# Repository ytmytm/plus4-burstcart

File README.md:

# BurstCart - Fast serial cartridge for C16/116/Plus4

This Plus/4 cartridge implements both fast serial burst for 1570/1571/1581 drives and a parallel connection for the 1541 drive, enabling high-speed data transfers.

<a href="https://www.youtube.com/watch?v=kfF7x9RVxz8" target="_blank">
 
 <p><small>Click for video</small></p>
</a>

## About

The project started as a response to a question from **[Plus/4 World Forum](https://plus4world.powweb.com/forum.php?postid=52378)**.

In order to use the Burst (fast serial) protocol as implemented on the C128, we need a bidirectional hardware serial port.

The published version uses VIA 6522 chips, which are still relatively easy to obtain. The additional logic addresses a VIA hardware bug that can lead to framing errors and lost bits when the serial port is externally clocked, as is the case with the fast serial burst protocol.

The single IEC port should be connected to the pass-through serial port on the last disk drive in the chain, looping back to the computer.

VIA Port A and lines CA1/CA2 are also used as a parallel connection for 1541 parallel burst with hardware handshake. The order of signals on the J3 connector for a ribbon cable is compatible with parallel cables known from the C64, particularly DolphinDOS.

VIA Port B is not used, except for bit 0, which controls the direction of the serial port.

Other attempts included in the repository are:

### CPLD

This is an attempt to drop legacy chips altogether.

Due to the limited number of gates, it only implements small parts of the CIA, such as timer A with a fixed rate, the hardware serial port, and the status register. The implementation does only what it necessary to make burst protocol work: to be able to send a byte via burst to enable burst protocol and to receive bytes on serial port with external clock.

### CIA (6526) - abandoned

This seemed obvious as CBM themselves added CIA just for this purpose to 1571. However, the timing differences made it impossible to use the CIA reliably with the screen on.

These chips are also hard to obtain.

The PCB had enough space for two IEC ports as a passthrough.

## Hardware

### VIA

KiCad 6.0 project files are available in the [`burstcart-via/kicad/`](burstcart-via/kicad/) directory.

Schematic is available as [`burstcart-via.pdf`](burstcart-via/kicad/plots/burstcart-via.pdf) in the `burstcart-via/kicad/plots/` directory.

Gerber files for manufacturing are available from [`burstcart-via/kicad/plots/`](burstcart-via/kicad/plots/) directory.

### CPLD

KiCad 6.0 project files are available in the [`burstcart-cpld/kicad/`](burstcart-cpld/kicad/) directory.

Schematic is available as [`burstcart-cpld.pdf`](burstcart-cpld/kicad/plots/burstcart-cpld-44.pdf) in the `burstcart-cpld/kicad/plots/` directory.

Gerber files for manufacturing are available from [`burstcart-cpld/kicad/plots/`](burstcart-cpld/kicad/plots/) directory.

## Firmware 

### VIA

The firmware for the GAL22V10 programmable logic device is provided as a compiled JEDEC file [`BURSTCART-VIA.jed`](burstcart-via/gal/BURSTCART-VIA.jed).

The source code for the GAL logic is written in CUPL and available as [`burstcart-via.pld`](burstcart-via/gal/burstcart-via.pld). This file contains the logic equations that implement the address decoding and serial port direction control.

The GAL firmware fixes VIA's address at `$FDA0-$FDAF` range.

### CPLD

The CPLD firmware is also provided as a compiled JEDEC file [`CIA.jed`](burstcart-cpld/hdl/ciasdr-hdl/cia.jed).

The source code is written in Verilog for XILINX ISE. All the project files are provided in [`ciasdr-hdl`](burstcart-cpld/hdl/ciasdr-hdl).

The firmware fixes CPLD address at `$FD90-$FD9F` range.

## Software

### EPROM

The GAL chip on the VIA version does not have enough space to support 64K ROMs as C1/C2 cartridges, so only 32K is visible to the computer at any given time as C1.

You can use 32K chips; for the 64K version, the 32K banks can be selected using a switch connected to JP4.

The CPLD version can address both C1 and C2 cartridges, so all 64K is available.

The **[Parobek](https://github.com/ytmytm/plus4-parobek)** project provides a ROM that supports various fastloaders for BurstCart:

- autodetected fast serial burst for 1570/1571/1581
- parallel cable loader for 1541
- even faster parallel cable loader for 1541 with [1541-RAMBOard](https://github.com/ytmytm/1541-RAMBOardII) patched ROM
- [tcbm2sd fastloader](https://github.com/ytmytm/plus4-tcbm2sd) for both device numbers
- 1551 fastloader for both device numbers
- DOS wedge
- embedded Directory Browser

Be sure to choose correct ROM version - for VIA or CPLD.

## VIA PCB jumpers

There are three jumpers on the VIA PCB:

- JP1 determines how the `/IRQ` line is connected to the VIA. For W65C22S, it should go through a diode; for all other 6522 versions, it can be connected directly, and `D1` can be omitted.
- JP2 chooses the clock for VIA - `phi0` or `phi2` (default)
- JP3 chooses the clock for GAL - `phi0` (default) or `phi2`
- JP4 controls line A15 for the EPROM and chooses which 32K half of a 64K ROM will appear as cartridge C1

## Theory of operation

### Fast serial

The burst mode protocol were originally developed by Commodore for the C128 and 1571/1581 drives. It uses the hardware serial port available on VIA and CIA chips. The data is transmitted over the IEC data line, with the hardware clock controlled by the sender and routed through the (otherwise unused) SRQ line. Changes in the IEC clock line are used as a handshake signal.

This was not available on the 1541 due to a hardware bug in the 6522 chips.

This project fixes the bug with a 74LS74 latch. Another 74LS126 chip is needed to buffer the input/output and provide the necessary open collector outputs on the external side for both the clock and data lines. The direction of the bus is controlled by port B bit 0 (PB0) pulled high to make it input as a default after reset.

The single IEC port on the VIA cartridge has only the hardware data and clock lines connected, as well as a common GND.

The CPLD cartridge has dual daisy-chained IEC ports, so you can connect the computer's serial port to cartridge and continue from the second port to all other IEC devices.

### Parallel cable

The 1541 drive's VIA#1 port A is unused. On the C64, this is connected to the User Port, along with two hardware handshake lines, providing the fastest possible connection between the VIA and CIA.

Here we connect it to port A as well. Note that on the BurstCart side, the handshake lines are connected to CA1/CA2 corresponding to port A, but to CA2/CB1 on the 1541 side. This is not symmetrical because on the 1541, CA1 from VIA#1 was already used for another purpose.

## Additional Resources

All files necessary for manufacturing, including Gerbers, schematic, GAL firmware, and ROM, can be found in the [GitHub releases section](https://github.com/ytmytm/plus4-burstcart/releases).

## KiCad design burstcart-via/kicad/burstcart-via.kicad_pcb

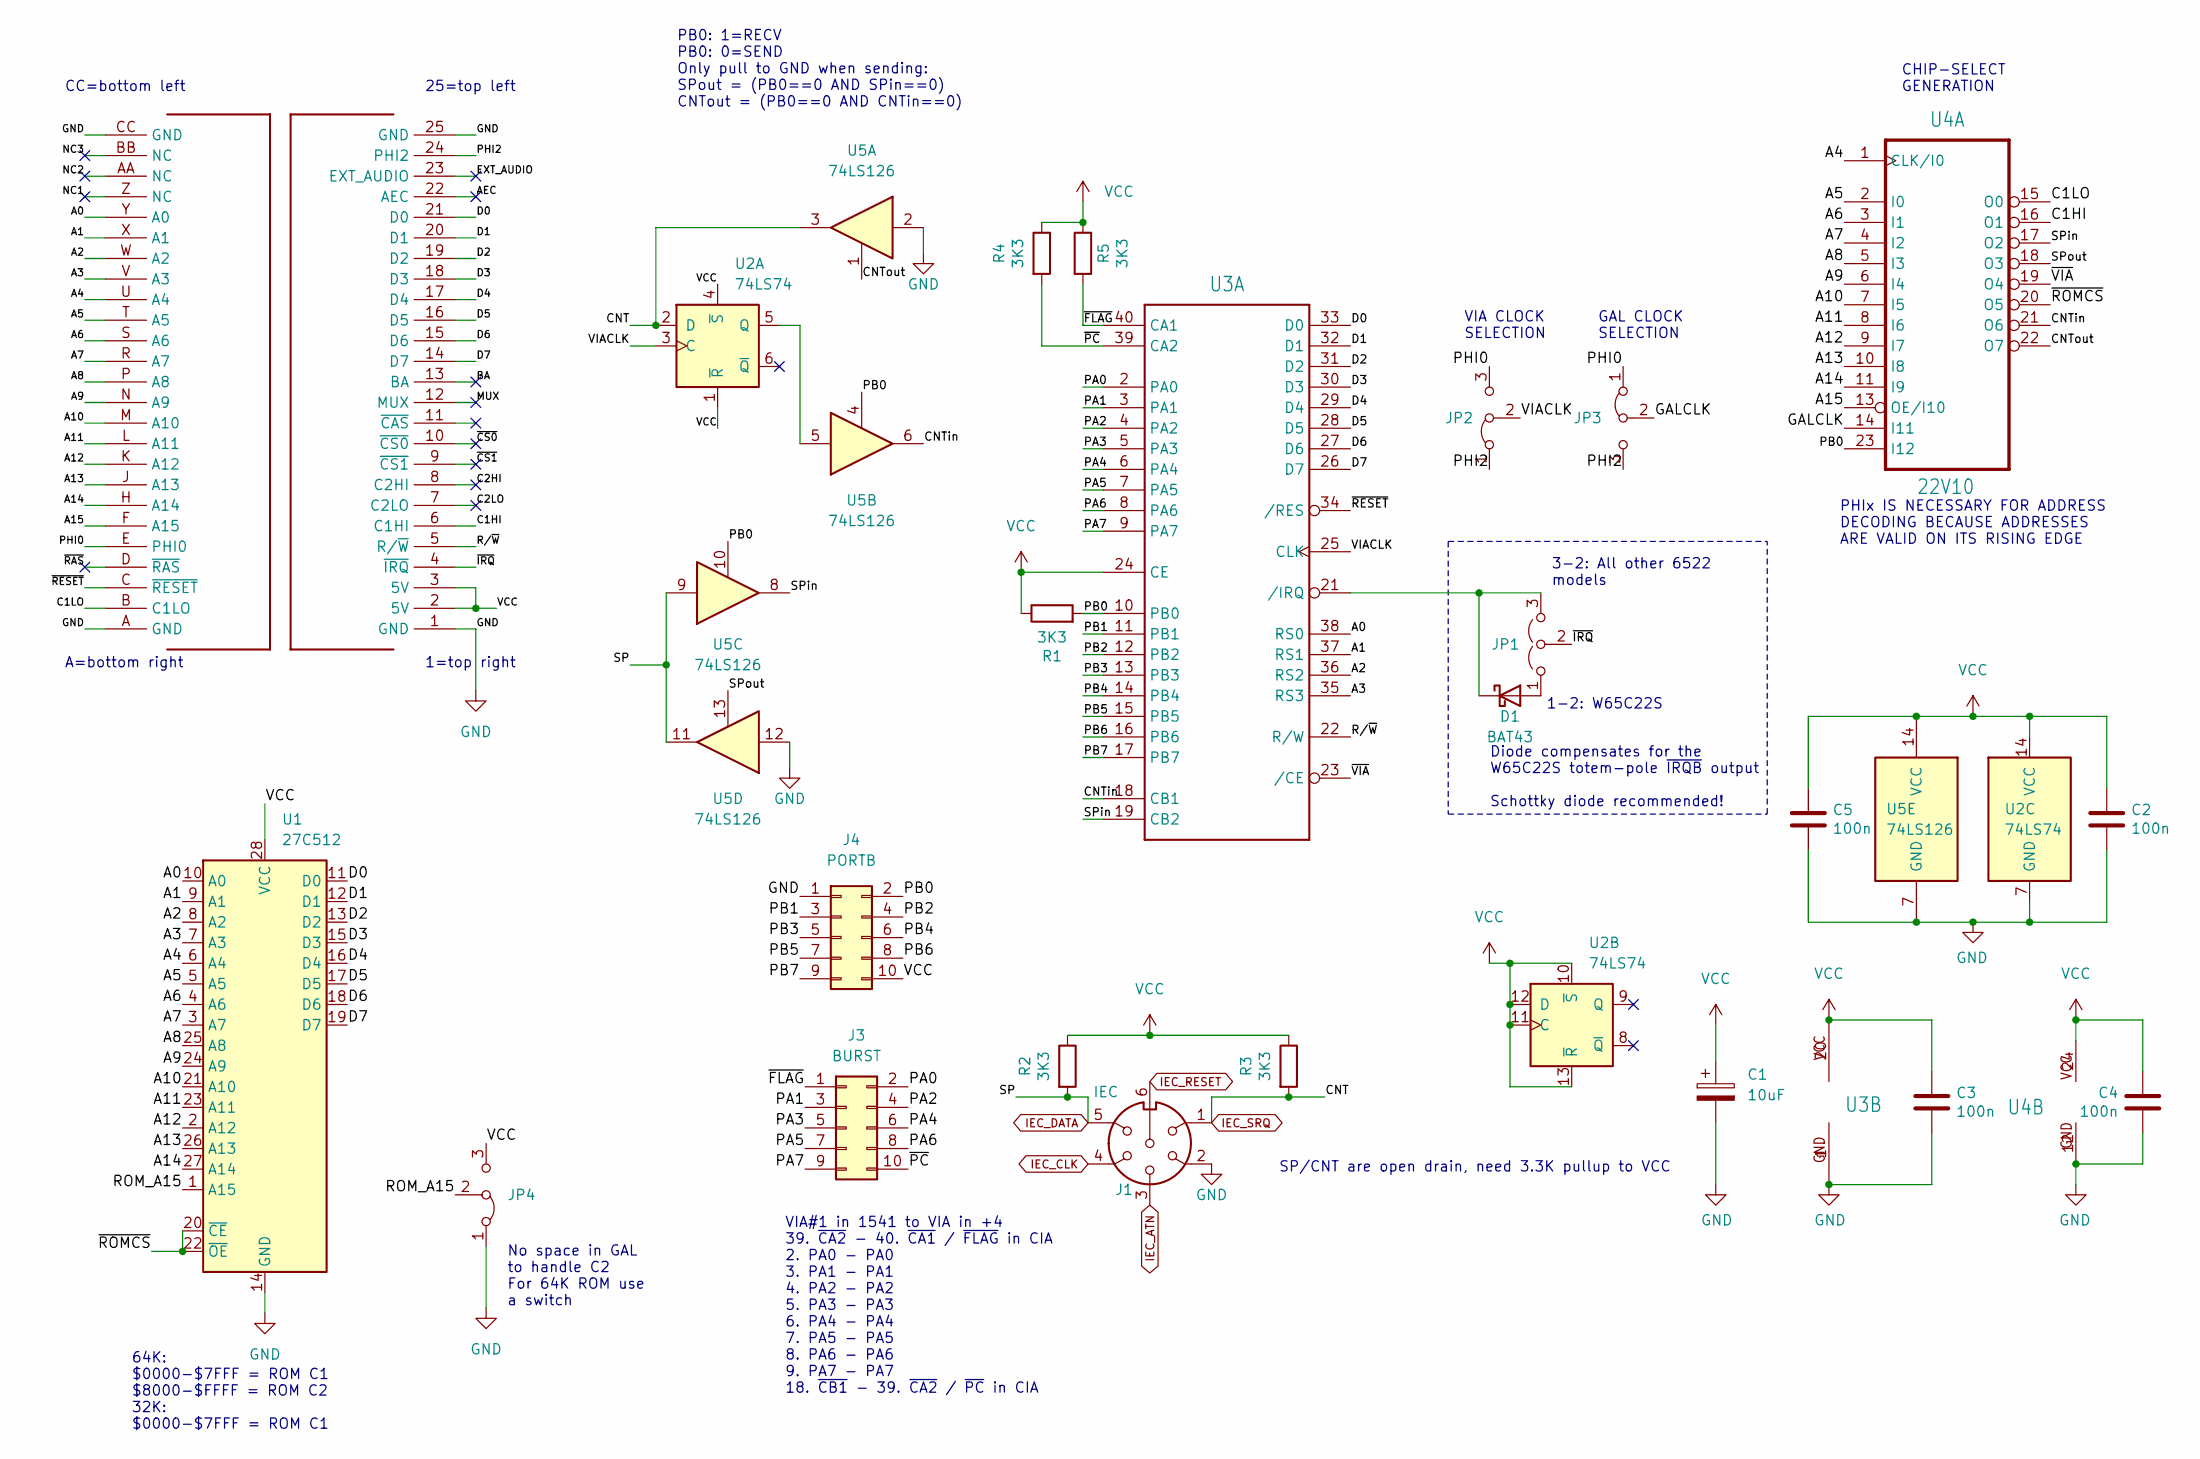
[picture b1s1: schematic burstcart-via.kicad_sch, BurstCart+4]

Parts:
C1: 10uF; CP_Radial_D5.0mm_P2.00mm
C2, C3, C4, C5: 470p; C_Disc_D7.0mm_W2.5mm_P5.00mm; MouserPN 810-FG28C0G1H471JNT6
D1: BAT43; D_DO-35_SOD27_P7.62mm_Horizontal
J1: IEC; DIN6
J3: BURST; PinHeader_2x05_P2.54mm_Vertical
J4: PORTB; PinHeader_2x05_P2.54mm_Vertical
JP1: Jumper_3_Open; SolderJumper-3_P1.3mm_Open_RoundedPad1.0x1.5mm_NumberLabels
JP2, JP3: Jumper_3_Bridged12; SolderJumper-3_P1.3mm_Bridged12_Pad1.0x1.5mm_NumberLabels
JP4: Jumper_3_Bridged12; PinHeader_1x03_P2.54mm_Vertical
R1, R2, R3, R4, R5: 3K3; R_Axial_DIN0207_L6.3mm_D2.5mm_P10.16mm_Horizontal
U1: 27C512; DIP-28_W15.24mm_Socket
U2: 74LS74; DIP-14_W7.62mm_Socket
U3: 6522; DIP-40_W15.24mm_Socket
U4: 22V10; DIP-24_W7.62mm_Socket
U5: 74LS126; DIP-14_W7.62mm_Socket
U$1: C16_CARTRIDGE; C16_CART

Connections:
/A0: U1.10 (A0), U3.38 (RS0), U$1.Y (A0)
/A1: U1.9 (A1), U3.37 (RS1), U$1.X (A1)
/A2: U1.8 (A2), U3.36 (RS2), U$1.W (A2)
/A3: U1.7 (A3), U3.35 (RS3), U$1.V (A3)
/A4: U1.6 (A4), U4.1 (CLK/I0), U$1.U (A4)
/A5: U1.5 (A5), U4.2 (I0), U$1.T (A5)
/A6: U1.4 (A6), U4.3 (I1), U$1.S (A6)
/A7: U1.3 (A7), U4.4 (I2), U$1.R (A7)
/A8: U1.25 (A8), U4.5 (I3), U$1.P (A8)
/A9: U1.24 (A9), U4.6 (I4), U$1.N (A9)
/A10: U1.21 (A10), U4.7 (I5), U$1.M (A10)
/A11: U1.23 (A11), U4.8 (I6), U$1.L (A11)
/A12: U1.2 (A12), U4.9 (I7), U$1.K (A12)
/A13: U1.26 (A13), U4.10 (I8), U$1.J (A13)
/A14: U1.27 (A14), U4.11 (I9), U$1.H (A14)
/A15: U4.13 (OE/I10), U$1.F (A15)
/AEC: U$1.22 (AEC)
/BA: U$1.13 (BA)
/C1HI: U4.16 (O1), U$1.6 (C1HI)
/C1LO: U4.15 (O0), U$1.B (C1LO)
/C2HI: U$1.8 (C2HI)
/C2LO: U$1.7 (C2LO)
/CNTin: U3.18 (CB1), U4.21 (O6), U5.6
/CNTout: U4.22 (O7), U5.1
/D0: U1.11 (D0), U3.33 (D0), U$1.21 (D0)
/D1: U1.12 (D1), U3.32 (D1), U$1.20 (D1)
/D2: U1.13 (D2), U3.31 (D2), U$1.19 (D2)
/D3: U1.15 (D3), U3.30 (D3), U$1.18 (D3)
/D4: U1.16 (D4), U3.29 (D4), U$1.17 (D4)
/D5: U1.17 (D5), U3.28 (D5), U$1.16 (D5)
/D6: U1.18 (D6), U3.27 (D6), U$1.15 (D6)
/D7: U1.19 (D7), U3.26 (D7), U$1.14 (D7)
/EXT_AUDIO: U$1.23 (EXT_AUDIO)
/GALCLK: JP3.2 (C), U4.14 (I11)
/MUX: U$1.12 (MUX)
/NC1: U$1.Z (NC)
/NC2: U$1.AA (NC)
/NC3: U$1.BB (NC)
/PA0: J3.2, U3.2 (PA0)
/PA1: J3.3, U3.3 (PA1)
/PA2: J3.4, U3.4 (PA2)
/PA3: J3.5, U3.5 (PA3)
/PA4: J3.6, U3.6 (PA4)
/PA5: J3.7, U3.7 (PA5)
/PA6: J3.8, U3.8 (PA6)
/PA7: J3.9, U3.9 (PA7)
/PB0: J4.2, R1.2, U3.10 (PB0), U4.23 (I12), U5.4, U5.10
/PB1: J4.3, U3.11 (PB1)
/PB2: J4.4, U3.12 (PB2)
/PB3: J4.5, U3.13 (PB3)
/PB4: J4.6, U3.14 (PB4)
/PB5: J4.7, U3.15 (PB5)
/PB6: J4.8, U3.16 (PB6)
/PB7: J4.9, U3.17 (PB7)
/PHI0: JP2.3 (B), JP3.1 (A), U$1.E (PHI0)
/PHI2: JP2.1 (A), JP3.3 (B), U$1.24 (PHI2)
/ROM_A15: JP4.2 (C), U1.1 (A15)
/R/~W: U3.22 (R/W), U$1.5 (R/~W)
/SPin: U3.19 (CB2), U4.17 (O2), U5.8
/SPout: U4.18 (O3), U5.13
/VIACLK: JP2.2 (C), U2.3 (C), U3.25 (CLK)
/~CS0: U$1.10 (~CS0)
/~CS1: U$1.9 (~CS1)
/~FLAG: J3.1, R5.2, U3.40 (CA1)
/~IRQ: JP1.2 (C), U$1.4 (~IRQ)
/~PC: J3.10, R4.2, U3.39 (CA2)
/~RAS: U$1.D (~RAS)
/~RESET: U3.34 (/RES), U$1.C (~RESET)
/~ROMCS: U1.20 (~CE), U1.22 (~OE), U4.20 (O5)
/~VIA: U3.23 (/CE), U4.19 (O4)
GND: C1.2, C2.2, C3.2, C4.2, C5.2, J1.2, J4.1, JP4.1 (A), U1.14 (GND), U2.7 (GND), U3.1 (GND), U4.12 (GND), U5.2, U5.7 (GND), U5.12, U$1.1 (GND), U$1.25 (GND), U$1.A (GND), U$1.CC (GND)
IEC_ATN: J1.3
IEC_CLK: J1.4
IEC_DATA: J1.5, R2.2, U5.9, U5.11
IEC_RESET: J1.6
IEC_SRQ: J1.1, R3.2, U2.2 (D), U5.3
unnamed: D1.2 (A), JP1.1 (A)
unnamed: D1.1 (K), JP1.3 (B), U3.21 (/IRQ)
unnamed: U2.5 (Q), U5.5
VCC: C1.1, C2.1, C3.1, C4.1, C5.1, J4.10, JP4.3 (B), R1.1, R2.1, R3.1, R4.1, R5.1, U1.28 (VCC), U2.1 (~R), U2.4 (~S), U2.10 (~S), U2.11 (C), U2.12 (D), U2.13 (~R), U2.14 (VCC), U3.20 (VCC), U3.24 (CE), U4.24 (VCC), U5.14 (VCC), U$1.2 (5V), U$1.3 (5V)

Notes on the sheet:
25=top left
Diode compensates for the W65C22S totem-pole ~{IRQB} output Schottky diode recommended!
VIA CLOCK SELECTION
1-2: W65C22S
A=bottom right
SP/CNT are open drain, need 3.3K pullup to VCC
VIA#1 in 1541 to VIA in +4 39. ~{CA2} - 40. ~{CA1} / ~{FLAG} in CIA 2. PA0 - PA0 3. PA1 - PA1 4. PA2 - PA2 5. PA3 - PA3 6. PA4 - PA4 7. PA5 - PA5 8. PA6 - PA6 9. PA7 - PA7 18. ~{CB1} - 39. ~{CA2} / ~{PC} in CIA
PB0: 1=RECV PB0: 0=SEND Only pull to GND when sending: SPout = (PB0==0 AND SPin==0) CNTout = (PB0==0 AND CNTin==0)
GAL CLOCK SELECTION
CHIP-SELECT GENERATION
CC=bottom left
No space in GAL to handle C2 For 64K ROM use a switch
3-2: All other 6522 models
1=top right
PHIx IS NECESSARY FOR ADDRESS DECODING BECAUSE ADDRESSES ARE VALID ON ITS RISING EDGE
64K: $0000-$7FFF = ROM C1 $8000-$FFFF = ROM C2 32K: $0000-$7FFF = ROM C1

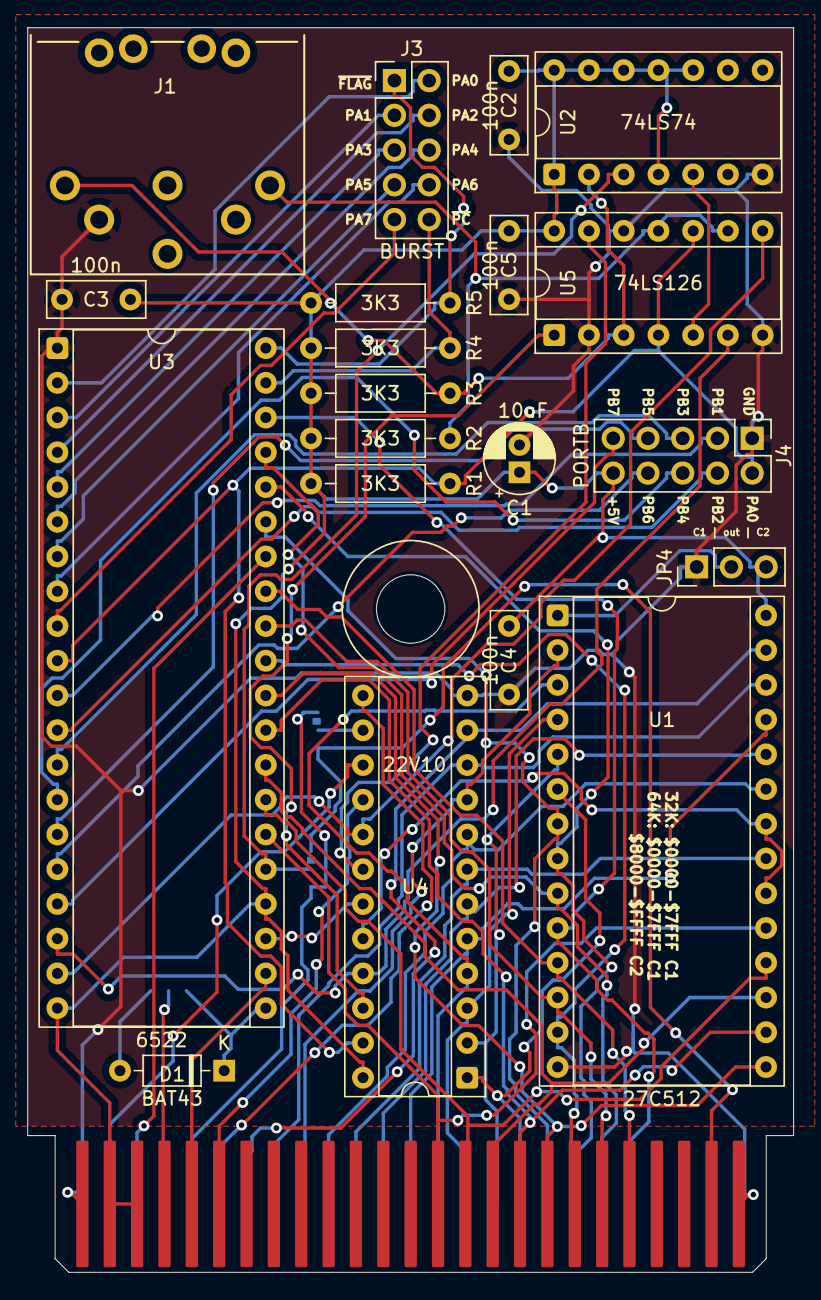
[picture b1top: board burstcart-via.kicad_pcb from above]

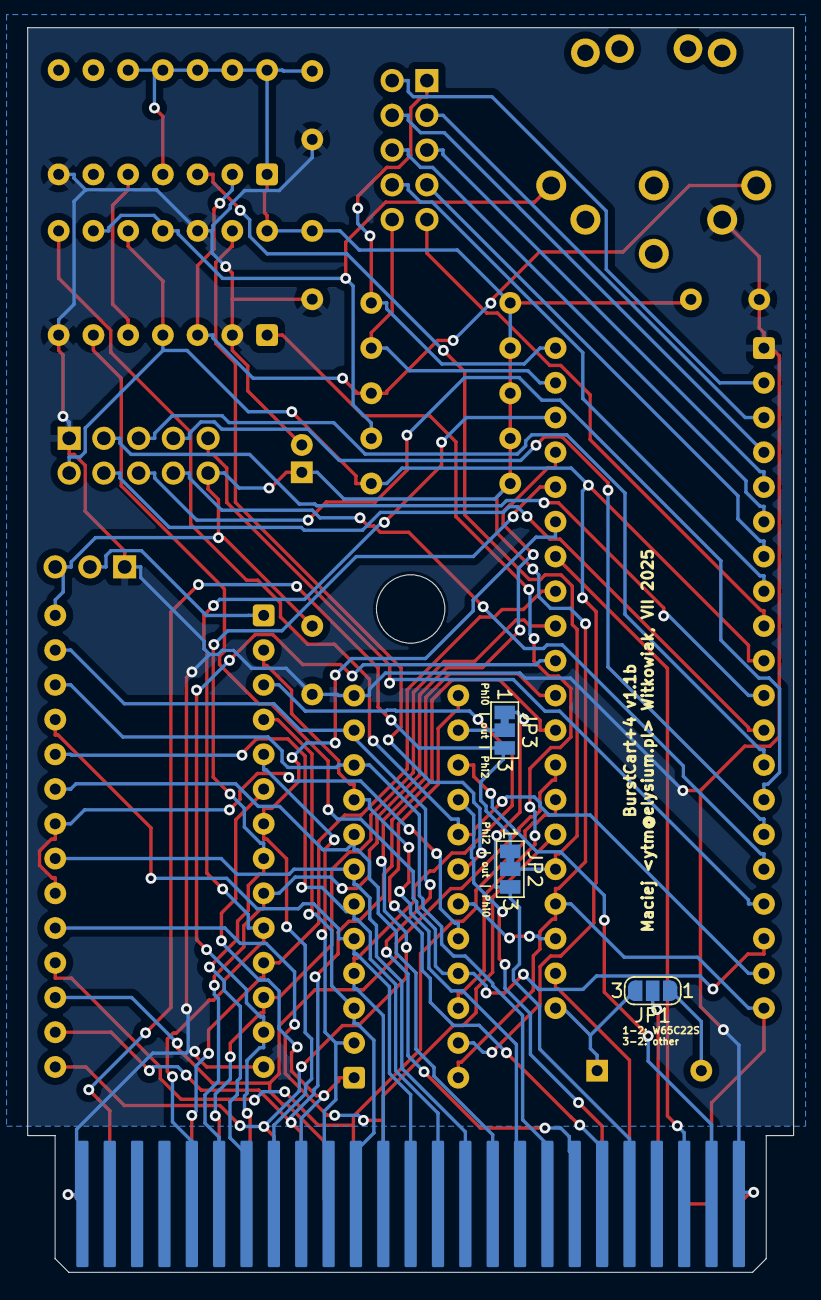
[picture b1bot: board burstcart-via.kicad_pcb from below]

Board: 2 copper layers, 56.0 x 91.0 mm, 24 parts (3 on the bottom side), 65 nets.

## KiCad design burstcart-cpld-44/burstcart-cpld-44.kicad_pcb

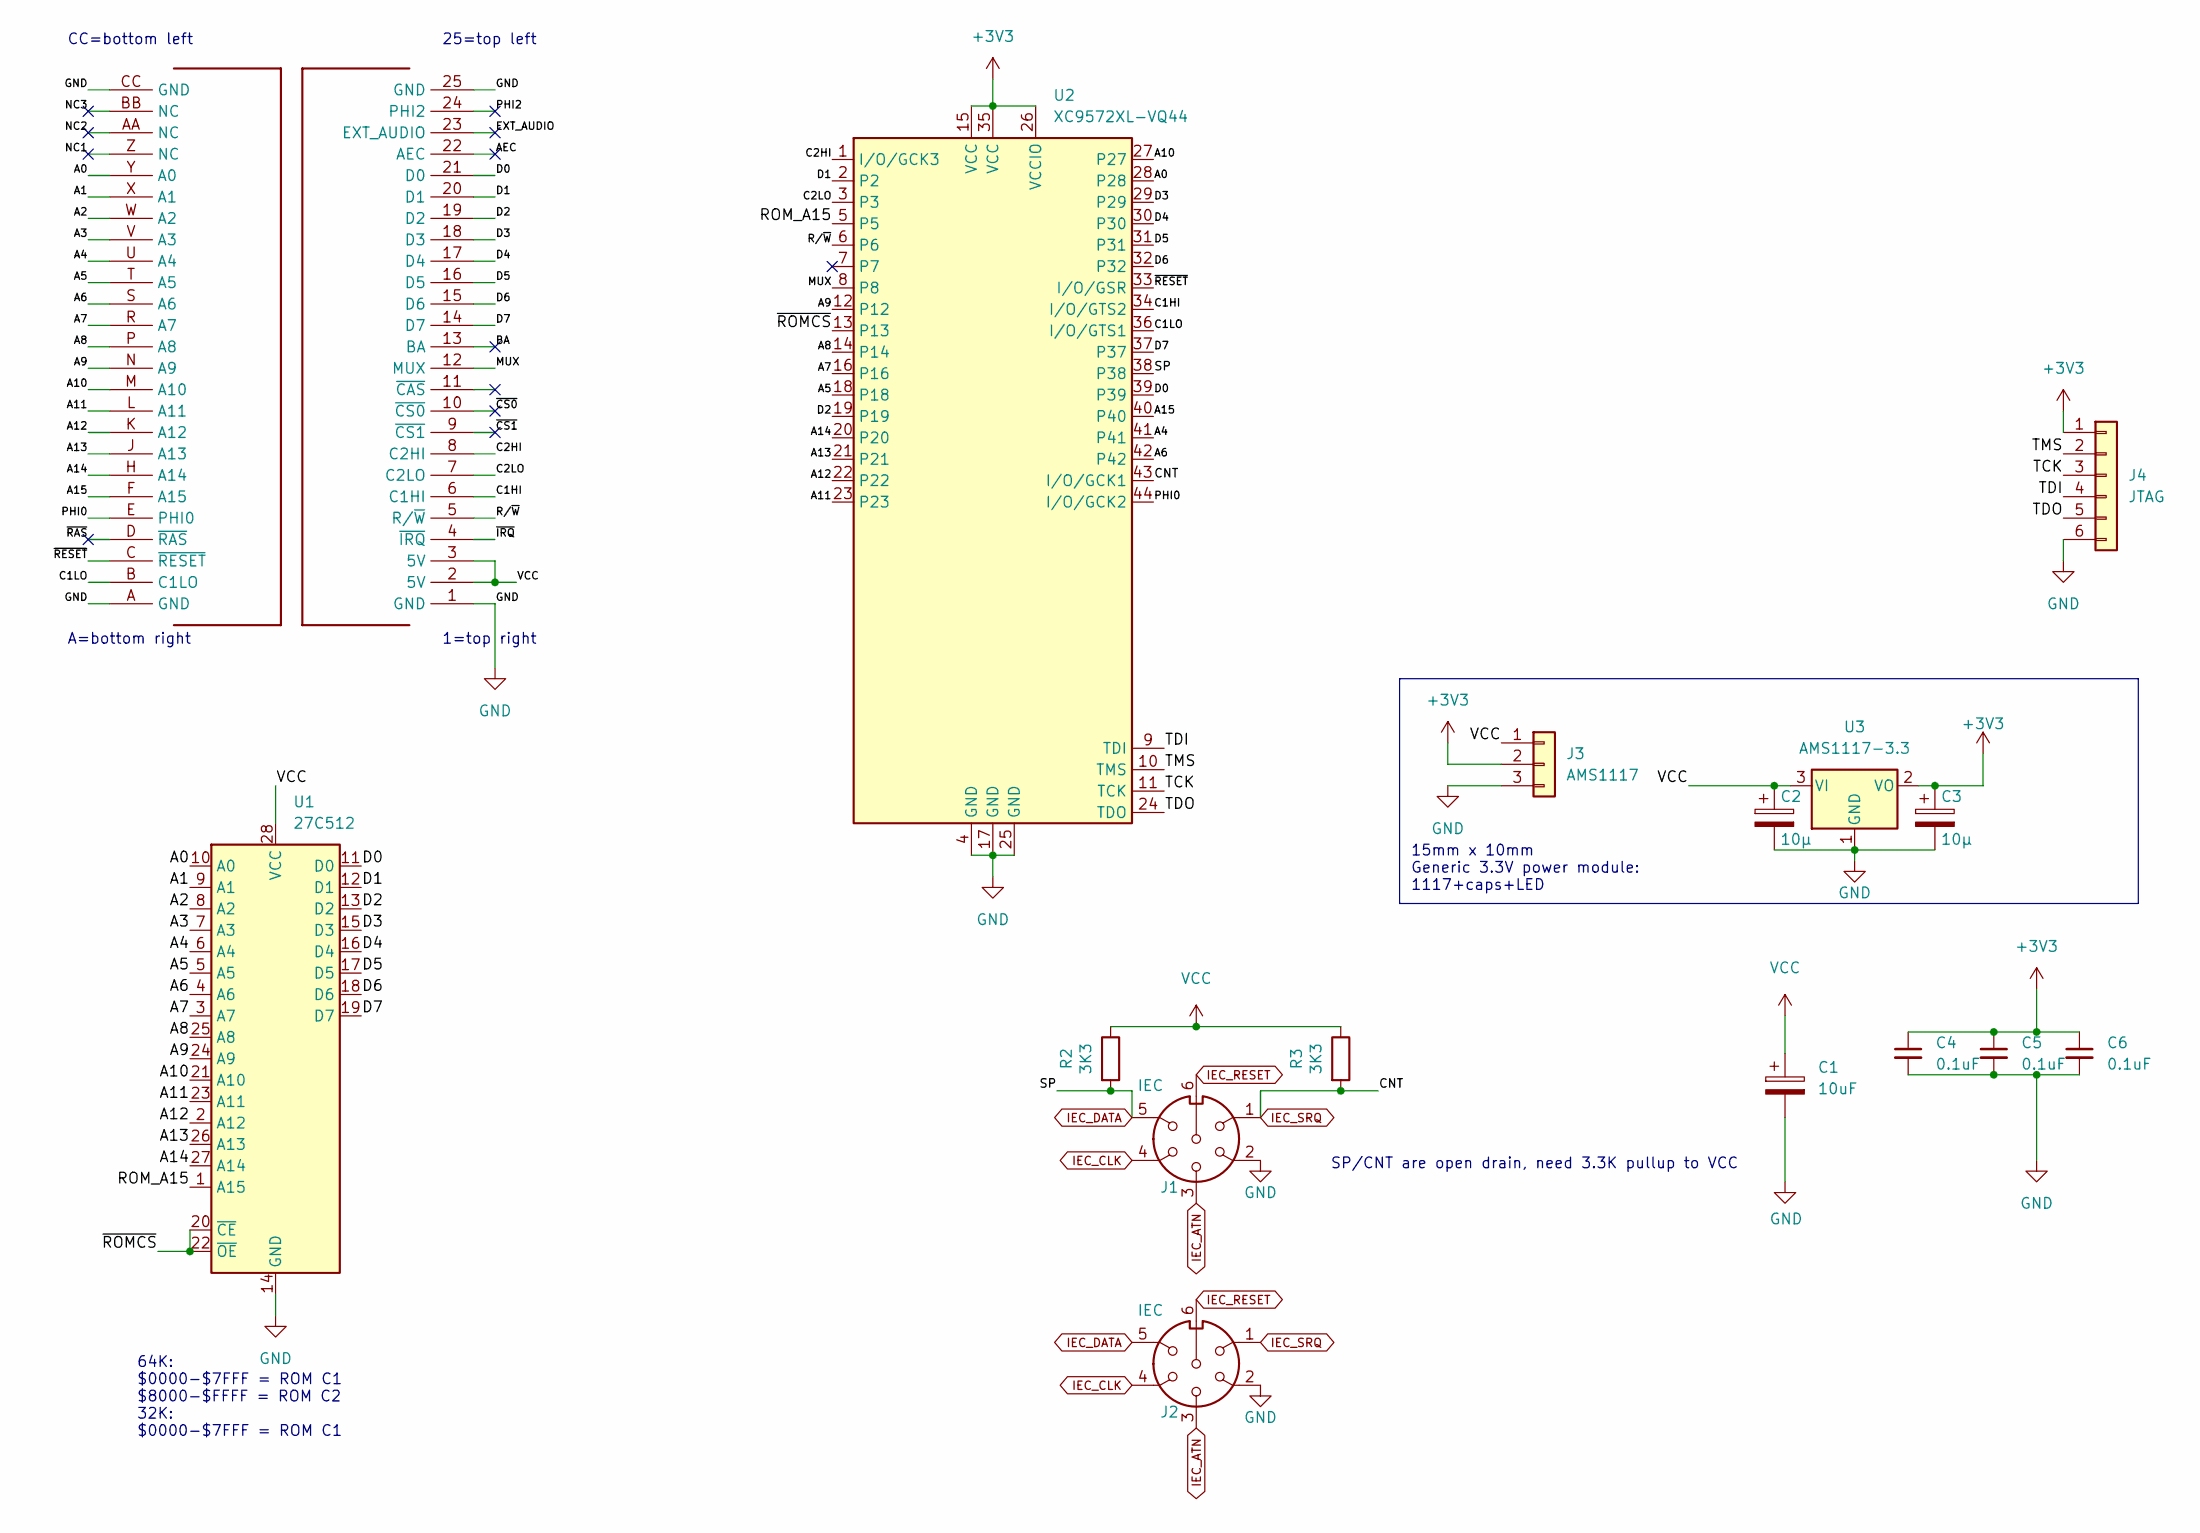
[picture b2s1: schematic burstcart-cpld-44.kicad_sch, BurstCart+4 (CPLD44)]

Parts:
C1: 10uF; CP_Radial_D5.0mm_P2.00mm
C2, C3: 10µ; CP_EIA-3216-12_Kemet-S_Pad1.58x1.35mm_HandSolder; JLCPCB Part # C1969735
C4, C5, C6: 0.1uF; C_0805_2012Metric_Pad1.18x1.45mm_HandSolder; JLCPCB Part # C49678
J1, J2: IEC; DIN6
J3: AMS1117; PinHeader_1x03_P2.54mm_Vertical
J4: JTAG; PinHeader_1x06_P2.54mm_Vertical
R2, R3: 3K3; R_0805_2012Metric_Pad1.20x1.40mm_HandSolder
U1: 27C512; DIP-28_W15.24mm_Socket
U2: XC9572XL-VQ44; TQFP-44_10x10mm_P0.8mm
U3: AMS1117-3.3; SOT-223-3_TabPin2; JLCPCB Part # C6186
U$1: C16_CARTRIDGE; C16_CART

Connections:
+3V3: C3.1, C4.1, C5.1, C6.1, J3.2, J4.1, U2.15 (VCC), U2.26 (VCCIO), U2.35 (VCC), U3.2 (VO)
/A0: U1.10 (A0), U2.28, U$1.Y (A0)
/A1: U1.9 (A1), U$1.X (A1)
/A2: U1.8 (A2), U$1.W (A2)
/A3: U1.7 (A3), U$1.V (A3)
/A4: U1.6 (A4), U2.41, U$1.U (A4)
/A5: U1.5 (A5), U2.18, U$1.T (A5)
/A6: U1.4 (A6), U2.42, U$1.S (A6)
/A7: U1.3 (A7), U2.16, U$1.R (A7)
/A8: U1.25 (A8), U2.14, U$1.P (A8)
/A9: U1.24 (A9), U2.12, U$1.N (A9)
/A10: U1.21 (A10), U2.27, U$1.M (A10)
/A11: U1.23 (A11), U2.23, U$1.L (A11)
/A12: U1.2 (A12), U2.22, U$1.K (A12)
/A13: U1.26 (A13), U2.21, U$1.J (A13)
/A14: U1.27 (A14), U2.20, U$1.H (A14)
/A15: U2.40, U$1.F (A15)
/AEC: U$1.22 (AEC)
/BA: U$1.13 (BA)
/C1HI: U2.34 (I/O/GTS2), U$1.6 (C1HI)
/C1LO: U2.36 (I/O/GTS1), U$1.B (C1LO)
/C2HI: U2.1 (I/O/GCK3), U$1.8 (C2HI)
/C2LO: U2.3, U$1.7 (C2LO)
/D0: U1.11 (D0), U2.39, U$1.21 (D0)
/D1: U1.12 (D1), U2.2, U$1.20 (D1)
/D2: U1.13 (D2), U2.19, U$1.19 (D2)
/D3: U1.15 (D3), U2.29, U$1.18 (D3)
/D4: U1.16 (D4), U2.30, U$1.17 (D4)
/D5: U1.17 (D5), U2.31, U$1.16 (D5)
/D6: U1.18 (D6), U2.32, U$1.15 (D6)
/D7: U1.19 (D7), U2.37, U$1.14 (D7)
/EXT_AUDIO: U$1.23 (EXT_AUDIO)
/MUX: U2.8, U$1.12 (MUX)
/NC1: U$1.Z (NC)
/NC2: U$1.AA (NC)
/NC3: U$1.BB (NC)
/PHI0: U2.44 (I/O/GCK2), U$1.E (PHI0)
/PHI2: U$1.24 (PHI2)
/ROM_A15: U1.1 (A15), U2.5
/R/~W: U2.6, U$1.5 (R/~W)
/TCK: J4.3, U2.11 (TCK)
/TDI: J4.4, U2.9 (TDI)
/TDO: J4.5, U2.24 (TDO)
/TMS: J4.2, U2.10 (TMS)
/~CS0: U$1.10 (~CS0)
/~CS1: U$1.9 (~CS1)
/~IRQ: U$1.4 (~IRQ)
/~RAS: U$1.D (~RAS)
/~RESET: U2.33 (I/O/GSR), U$1.C (~RESET)
/~ROMCS: U1.20 (~CE), U1.22 (~OE), U2.13
GND: C1.2, C2.2, C3.2, C4.2, C5.2, C6.2, J1.2, J2.2, J3.3, J4.6, U1.14 (GND), U2.4 (GND), U2.17 (GND), U2.25 (GND), U3.1 (GND), U$1.1 (GND), U$1.25 (GND), U$1.A (GND), U$1.CC (GND)
IEC_ATN: J1.3, J2.3
IEC_CLK: J1.4, J2.4
IEC_DATA: J1.5, J2.5, R2.2, U2.38
IEC_RESET: J1.6, J2.6
IEC_SRQ: J1.1, J2.1, R3.2, U2.43 (I/O/GCK1)
VCC: C1.1, C2.1, J3.1, R2.1, R3.1, U1.28 (VCC), U3.3 (VI), U$1.2 (5V), U$1.3 (5V)

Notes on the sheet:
25=top left
A=bottom right
SP/CNT are open drain, need 3.3K pullup to VCC
CC=bottom left
15mm x 10mm Generic 3.3V power module: 1117+caps+LED
1=top right
64K: $0000-$7FFF = ROM C1 $8000-$FFFF = ROM C2 32K: $0000-$7FFF = ROM C1

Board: 2 copper layers, 16 parts (0 on the bottom side), 46 nets, no tracks yet.

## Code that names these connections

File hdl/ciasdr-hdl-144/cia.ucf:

#PINLOCK_BEGIN

#Tue May  6 21:23:17 2025

NET "A<0>"           LOC =  "S:PIN89";
NET "A<10>"          LOC =  "S:PIN90";
NET "A<11>"          LOC =  "S:PIN86";
NET "A<12>"          LOC =  "S:PIN91";
NET "A<13>"          LOC =  "S:PIN92";
NET "A<14>"          LOC =  "S:PIN82";
NET "A<15>"          LOC =  "S:PIN81";
NET "A<1>"           LOC =  "S:PIN80";
NET "A<2>"           LOC =  "S:PIN94";
NET "A<3>"           LOC =  "S:PIN79";
NET "A<4>"           LOC =  "S:PIN78";
NET "A<5>"           LOC =  "S:PIN96";
NET "A<6>"           LOC =  "S:PIN77";
NET "A<7>"           LOC =  "S:PIN76";
NET "A<8>"           LOC =  "S:PIN72";
NET "A<9>"           LOC =  "S:PIN71";
NET "E_CLK"          LOC =  "S:PIN23";
NET "MUX"            LOC =  "S:PIN85";
NET "RESET_n"        LOC =  "S:PIN1";
NET "RW"             LOC =  "S:PIN6";
NET "aec"            LOC =  "S:PIN66";
NET "ba"             LOC =  "S:PIN65";
NET "c1hi"           LOC =  "S:PIN95";
NET "c1lo"           LOC =  "S:PIN97";
NET "c2hi"           LOC =  "S:PIN73";
NET "c2lo"           LOC =  "S:PIN70";
NET "phi2"           LOC =  "S:PIN64";
NET "_unused"        LOC =  "S:PIN11";
NET "SP"             LOC =  "S:PIN63";
NET "IRQ_n"          LOC =  "S:PIN87";
NET "CNT"            LOC =  "S:PIN22";
NET "_resetout"      LOC =  "S:PIN93";
NET "D<0>"           LOC =  "S:PIN74";
NET "D<1>"           LOC =  "S:PIN10";
NET "D<2>"           LOC =  "S:PIN2";
NET "D<3>"           LOC =  "S:PIN3";
NET "D<4>"           LOC =  "S:PIN4";
NET "D<5>"           LOC =  "S:PIN7";
NET "D<6>"           LOC =  "S:PIN8";
NET "D<7>"           LOC =  "S:PIN9";
NET "rom_a15"        LOC =  "S:PIN24";
NET "rom_cs"         LOC =  "S:PIN68";
#PINLOCK_END

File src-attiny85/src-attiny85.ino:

// IDE: ATtiny25/45/85, internal 1MHz
// 1MHz is the default speed, no need to switch fuses to 8MHz
// compile to HEX (Sketch->Export compiled binary) and burn using TL866-II

// pinout
//                                /RESET 1  U  8 5V
// -- selector (floating or GND)  A3/PB3 2     7 A1/2/PB2
//                                A2/PB4 3     6 PB1 PWM
//                                   GND 4     5 PB0 PWM -- output PWM 50Hz

/* -D CKDIV8
board = attiny85
board_build.f_cpu = 1000000L
board_fuses.lfuse = 0x62
board_fuses.hfuse = 0xdf
board_fuses.efuse = 0xff
*/

const uint8_t PWM_pin = 0; // PB0, pin 5
const uint8_t mode_pin = 3; // PB3, pin 2 - jumper to GND for NTSC mode, keep floating (internal pullup) for PAL
uint8_t half_duty = 10;    // 10ms for PAL, 8ms for NTSC = 20ms/16ms

// use PAL (50Hz) clock, otherwise we would have to maintain two ROM versions

// Define OCR0A values and prescaler based on CKDIV8
#if F_CPU == 1000000L
  // 1MHz clock settings
  #define PRESCALER_BITS ((1 << CS01) | (1 << CS00))  // Prescaler = 64
  #define OCR0A_50HZ     155  // 50Hz: 1MHz / (2*64*(155+1)) ≈ 50.08Hz
  #define OCR0A_60HZ     129  // 60Hz: 1MHz / (2*64*(129+1)) ≈ 60.1Hz
#else
  // 8MHz clock settings
  #define PRESCALER_BITS ((1 << CS02) | (1 << CS00))  // Prescaler = 1024
  #define OCR0A_50HZ     77   // 50Hz: 8MHz / (2*1024*(77+1)) ≈ 50.08Hz
  #define OCR0A_60HZ     64   // 60Hz: 8MHz / (2*1024*(64+1)) ≈ 60.14Hz
#endif

void setup() {
  pinMode(PWM_pin, OUTPUT);
  digitalWrite(PWM_pin, LOW);
  pinMode(mode_pin, INPUT_PULLUP);
  delay(200);
  if (digitalRead(mode_pin) == LOW) { // is it tied to GND? yes - use software clock
    while (true) {
      delay(half_duty); // 10ms - half of 20ms duty cycle
      digitalWrite(PWM_pin, HIGH);
      delay(half_duty); // 10ms - half of 20ms duty cycle
      digitalWrite(PWM_pin, LOW);
    }
  }
  // otherwise use h/w clock
    DDRB |= (1 << PB0);    // PB0 (OC0A) as output

    // Configure Timer0 for CTC mode (toggle OC0A on compare match)
    TCCR0A = (1 << COM0A0) | (1 << WGM01);  // Toggle OC0A, CTC mode
    TCCR0B = PRESCALER_BITS;  // Set prescaler (64 or 1024)
    OCR0A = OCR0A_50HZ;

    while (1) { }
}

void loop() {
  // could be done using PWM and clock prescalers, but that is good enough for me
}

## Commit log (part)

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2025-04-22 notes
2025-04-22 ROM code
2025-04-23 ported Pasi Ojala's fastloader code
2025-04-30 simplify logic - define active low signals as such ; move /CIA from 22 to 19 ; move /ROM_A15 from 19 to 22
2025-05-01 comment
2025-05-01 loader works, only with blank screen (fast clock)
2025-05-01 updated docs
2025-05-01 PAL/NTSC software/hardware clock
2025-05-01 remarks about changes for v1.1
2025-05-01 - +5V net removed, all is VCC now - /CIA is pin 19, /ROM_A15 pin 22 now - default jumper shorted to reset CD4520 - default jumper shorted to phi2 for CIACLK - GAL is 22V10 - removed MUX connection to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
2025-05-02 renamed burstcart to burstcart-cia
2025-05-02 plot for v1.1
2025-05-02 link
2025-05-04 force slow clock for CIA register accesses
2025-05-04 note about 1551/tcbm2sd check for ROM fastloader
2025-05-06 PCB for VIA option
2025-05-06 CPLD remarks
2025-05-06 https://github.com/niklasekstrom/cia-verilog/blob/master/cia.v trimmed down to CPLD
2025-05-06 locked pins in UCF file, set smaller device to VQ44
2025-05-06 KiCad project for xc9572xl-vq44 (cpld-44)
2025-05-07 finalized VIA board
2025-05-07 finalized CPLD (VQ44) board
2025-05-07 finalized v1.1 cia board too
2025-05-07 check for TCBM device and fall back on ROM if detected
2025-05-07 reference fastloaders: hypaload 1551 v4, tcbm2sd, burst C64, speeddos C64/1541, hybraload+4 (+4 1541)
2025-05-11 adapt CIA code to CPLD registers, option to choose between CIA/VIA/CPLD
2025-05-11 untested VIA code
2025-05-28 combine register writes into single expression
2025-05-28 VIA 6522 datasheets
2025-05-28 NOT tested - should retain shift_out complete flag until register read
2025-05-29 timer reduced to 1 bit
2025-05-29 shift completed flag cleared on register write, data register read
2025-05-29 update comments
2025-05-29 proper sequence of reads/writes to clear status flag
2025-06-08 status
2025-06-08 reorganize project folders into -cia, -via, -cpld44
2025-06-08 conditional output filename
2025-06-08 fall back on tcbm2sd quasiburst loader, then on ROM for 1551
2025-06-08 restore secondary address from buffer
2025-06-08 cleanup
2025-06-08 correct shitft register access according to datasheet
2025-06-08 remove debug parts: slow clock for CIA and conditional screen blank
2025-06-08 hypaloaded for 1551 based on HypaLoad v4.7
2025-06-11 support for 1551 hypaload fastloader and tcbm2sd fastload utility
2025-06-16 startup screen like Action Replay
2025-06-17 fixed load error bug
2025-06-17 embed directory browser (from tcbm2sd) into ROM
2025-06-18 universal function key installer
2025-06-19 fixed load return status issues
2025-06-19 DOS wedge
2025-06-20 @8 thru @19 to set current device number
2025-06-21 dload, dsave shortcuts
2025-06-21 copy piece of code that checks if file exists from hypaload to tcbm2sd fastloader
2025-06-22 use patched directory browser, which keeps low code in tape buffer so that wedge area is not touched
2025-06-22 info about 1541+parallel port turbo (PortTurbo V1)
2025-06-24 remarks about parallel 1541
2025-06-24 detect 1541 with parallel cable and parallel cable interface (PIO/PPI/VIA/CIA)
2025-06-24 better check for VIA/CIA presence
2025-06-24 correct return value
2025-06-24 wrap debug in conditional
2025-06-24 factor out common parts and labels
2025-06-24 t2sd preserve border color
2025-06-24 factor out common code
2025-06-25 1541 parallel port loader, based on Port-Turbo_V1 (can load once)
2025-06-26 fixed DLOAD after DLOAD bug for 1541 parallel loader
2025-06-26 make sure that directory browser can coexist with loaders ; (D4 is load&run flag, copied to $8F)
2025-06-27 support for drive 9 on TCBM bus (1551 hypaload, tcbm2sd)
2025-06-27 1541 parallel test results with VIA (detection success, load fail)
2025-06-29 1541 parallel loader based on SpeedDOS+ PLUS
2025-06-29 loads first sector only
2025-06-29 preserve X (next track number)
2025-06-29 final touches to make it work
2025-06-29 inline .SpeedDOS_GetParallelByte to get data faster
2025-06-29 dump of ROM code for SpeedDos+ Plus (40 tracks)
2025-06-29 inline byte sending for small speed gain
2025-06-29 tested with PIO interface; VIA set for software handshake
2025-06-29 assemble and choose CIA/VIA version
2025-06-29 provisions for h/w handshake for VIA (to be tested and enabled on both ends after loader works)
2025-06-29 correct zoning
2025-06-29 setup VIA hardware handshake, test results on real h/w
2025-06-29 VIA handshake remarks, +4 side maybe has to be initialized with $0A, not $0B in viabase+12; consider enabling latching input on CA1 by $01 in viabase+11
2025-06-30 make halftrack sequence local (forgot that it's in SpeedDOS 1541 ROM)
2025-06-30 more comments
2025-06-30 patch to make it work with jiffy dos (not sure about jiffydos with 32K RAM patch)
2025-07-01 set correct CA1 edge, enable latching on input and set screen off
2025-07-01 explanation
2025-07-01 cleanup after load to make it work multiple times (GEOS does the same)
2025-07-01 device not present check
2025-07-01 make '$' use current drive
2025-07-01 make '/' load from current drive, to file loadaddress
2025-07-01 fixed preserving screen on/off status and secondary address for ROM load
2025-07-05 support for 1541 RAMBOard][ TrackCache ROM with embedded SpeedDOS loader, see https://github.com/ytmytm/1541-RAMBOardII
2025-07-06 ROM renamed as Parobek and moved to its own repo at https://github.com/ytmytm/plus4-parobek
2025-07-07 corrected JP4 to connect to Phi0 by default, corrected silkscreen texts ; updated to KiCad9
2025-07-08 link to releases
